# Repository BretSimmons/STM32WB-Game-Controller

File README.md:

# STM32WB Game Controller

Custom microcontroller for running embedded games and other programming projects.

**Functionality:**

My original idea for this board was to create a microcontroller to run an embedded pong game I wrote a few months ago [(here)](https://github.com/BretSimmons/Embedded-Pong). I ended up adding the requried perhipherals (I2C, ADC, and 4 GPIO pins), but also UART, and a connector for an RF antenna. I wanted to create a multi purpose microcontroller I can use in future projects, and gain experience impedence matching traces for high frequencies.

**How It Works:**

The board is powered by an USB-C header and runs through ESD protection and a step down voltage regulator to power the STM32WB55xx MCU. The MCU can be programmed via either the USB or a Tag Connect header. The MCU contains several internal clocks, and I additionally included an external crystal oscillator. The perhipherals can be configured via software, and routed out via the Molex headers on the board. 

**Future Updates:**

This project is a work in progress, and there are still a couple of changes I want to make before ordering the PCB. Once I have it ordered and assembled I will update this repo with a video demo.

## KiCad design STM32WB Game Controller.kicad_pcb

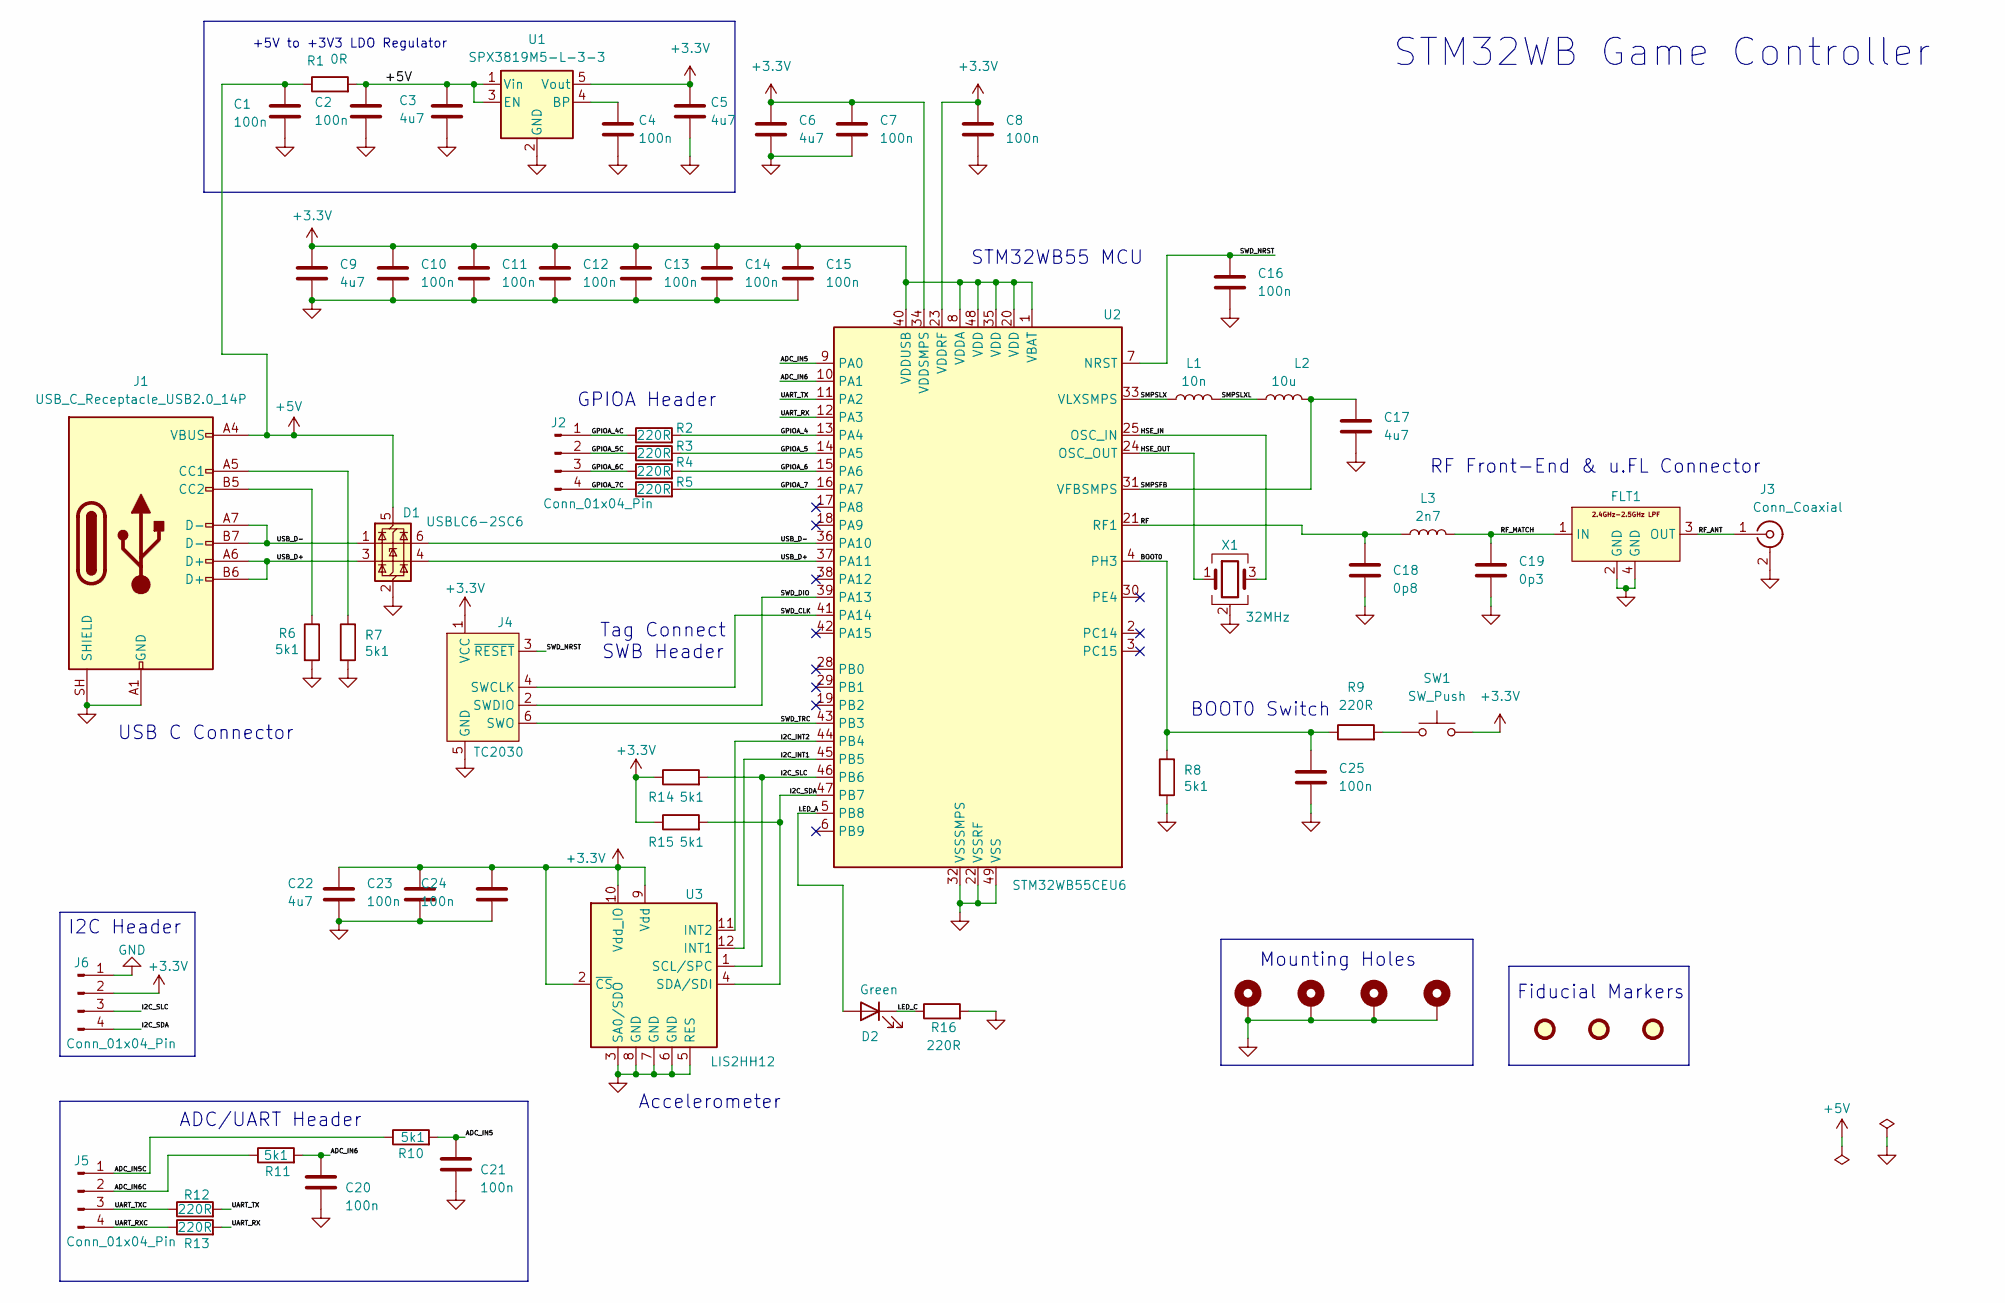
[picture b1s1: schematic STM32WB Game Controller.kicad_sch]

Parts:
C1, C2, C4, C7, C8, C10, C11, C12, C13, C14, C15, C16, C20, C21, C23, C24, C25: 100n; C_0603_1608Metric; Manufacturer Part Number CC0603JRX7R9BB104
C3, C5, C6, C9, C17, C22: 4u7; C_0805_2012Metric; Manufacturer Part Number CL21A475KPFNNNE
C18: 0p8; C_0603_1608Metric; Manufacturer Part Number CC0603BRNPO9BNR80
C19: 0p3; C_0603_1608Metric; Manufacturer Part Number 0603N0R3C500CT
D1: USBLC6-2SC6; SOT-23-6; Manufacturer Part Number USBLC6-2SC6
D2: Green; LED_0603_1608Metric; Manufacturer Part Number KT EELP41.12-S2U1-25-2X4X-5-R18
FID1, FID2, FID3: Fiducial; Fiducial_1mm_Mask2mm
FLT1: DLF162500LT-5028A1; Manufacturer Part Number DLF162500LT-5028A1
H1, H2, H3, H4: MountingHole_Pad; MountingHole_2.2mm_M2_Pad
J1: USB_C_Receptacle_USB2.0_14P; USB_C_Receptacle_GCT_USB4105-xx-A_16P_TopMnt_Horizontal; Manufacturer Part Number USB4105-GF-A
J2, J5, J6: Conn_01x04_Pin; Molex_PicoBlade_53048-0410_1x04_P1.25mm_Horizontal; Manufacturer Part Number 53048-0410
J3: Conn_Coaxial; U.FL_Hirose_U.FL-R-SMT-1_Vertical; Manufacturer Part Number U.FL-R-SMT(01)
J4: TC2030; Tag-Connect_TC2030-IDC-FP_2x03_P1.27mm_Vertical
L1: 10n; L_0603_1608Metric; Manufacturer Part Number LCCI0603J10NGTAR
L2: 10u; L_0805_2012Metric; Manufacturer Part Number MLZ2012M100WT000
L3: 2n7; L_0603_1608Metric; Manufacturer Part Number MCL1608V2-2R7-R
R1: 0R; R_0603_1608Metric; Manufacturer Part Number AF0603JR-130RL
R2, R3, R4, R5, R9, R12, R13, R16: 220R; R_0603_1608Metric; Manufacturer Part Number AF0603FR-07220RL
R6, R7, R8, R10, R11, R14, R15: 5k1; R_0603_1608Metric; Manufacturer Part Number RC0603FR-105K1L
SW1: SW_Push; SW_SPST_CK_RS282G05A3; Manufacturer Part Number RS-282G05A3-SM RT
U1: SPX3819M5-L-3-3; SOT-23-5; Manufacturer Part Number SPX3819M5-L-3-3/TR
U2: STM32WB55CEU6; QFN-48-1EP_7x7mm_P0.5mm_EP5.6x5.6mm; Manufacturer Part Number STM32WB55CEU6
U3: LIS2HH12; LGA-12_2x2mm_P0.5mm; Manufacturer Part Number LIS2HH12TR
X1: 32MHz; Crystal_SMD_2016-4Pin_2.0x1.6mm; Manufacturer Part Number CX2016SA32000F0HPQG1

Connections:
+3.3V: C5.1, C6.1, C7.1, C8.1, C9.1, C10.1, C11.1, C12.1, C13.1, C14.1, C15.1, C22.1, C23.1, C24.1, J4.1 (VCC), J6.2, R14.1, R15.1, SW1.2, U1.5 (Vout), U2.1 (VBAT), U2.8 (VDDA), U2.20 (VDD), U2.23 (VDDRF), U2.34 (VDDSMPS), U2.35 (VDD), U2.40 (VDDUSB), U2.48 (VDD), U3.2 (~CS), U3.9 (Vdd), U3.10 (Vdd_IO)
+5V: C1.1, C2.1, C3.1, D1.5 (VBUS), J1.A4 (VBUS), J1.A9 (VBUS), J1.B4 (VBUS), J1.B9 (VBUS), R1.1, R1.2, U1.1 (Vin), U1.3 (EN)
/ADC_IN5: C21.1, R10.2, U2.9 (PA0)
/ADC_IN5C: J5.1, R10.1
/ADC_IN6: C20.1, R11.2, U2.10 (PA1)
/ADC_IN6C: J5.2, R11.1
/BOOT0: C25.1, R8.1, R9.1, U2.4 (PH3)
/GPIOA_4: R2.2, U2.13 (PA4)
/GPIOA_4C: J2.1, R2.1
/GPIOA_5: R3.2, U2.14 (PA5)
/GPIOA_5C: J2.2, R3.1
/GPIOA_6: R4.2, U2.15 (PA6)
/GPIOA_6C: J2.3, R4.1
/GPIOA_7: R5.2, U2.16 (PA7)
/GPIOA_7C: J2.4, R5.1
/HSE_IN: U2.25 (OSC_IN), X1.3
/HSE_OUT: U2.24 (OSC_OUT), X1.1
/I2C_INT1: U2.45 (PB5), U3.12 (INT1)
/I2C_INT2: U2.44 (PB4), U3.11 (INT2)
/I2C_SDA: J6.4, R15.2, U2.47 (PB7), U3.4 (SDA/SDI)
/I2C_SLC: J6.3, R14.2, U2.46 (PB6), U3.1 (SCL/SPC)
/LED_A: D2.2 (A), U2.5 (PB8)
/LED_C: D2.1 (K), R16.1
/RF: C18.1, L3.1, U2.21 (RF1)
/RF_ANT: FLT1.3 (OUT), J3.1 (In)
/RF_MATCH: C19.1, FLT1.1 (IN), L3.2
/SMPSFB: C17.1, L2.2, U2.31 (VFBSMPS)
/SMPSLX: L1.1, U2.33 (VLXSMPS)
/SMPSLXL: L1.2, L2.1
/SWD_CLK: J4.4 (SWCLK), U2.41 (PA14)
/SWD_DIO: J4.2 (SWDIO), U2.39 (PA13)
/SWD_NRST: C16.1, J4.3 (~RESET), U2.7 (NRST)
/SWD_TRC: J4.6 (SWO), U2.43 (PB3)
/UART_RX: R13.2, U2.12 (PA3)
/UART_RXC: J5.4, R13.1
/UART_TX: R12.2, U2.11 (PA2)
/UART_TXC: J5.3, R12.1
/USB_D+: D1.3 (I/O2), D1.4 (I/O2), J1.A6 (D+), J1.B6 (D+), U2.37 (PA11)
/USB_D-: D1.1 (I/O1), D1.6 (I/O1), J1.A7 (D-), J1.B7 (D-), U2.36 (PA10)
GND: C1.2, C2.2, C3.2, C4.2, C5.2, C6.2, C7.2, C8.2, C9.2, C10.2, C11.2, C12.2, C13.2, C14.2, C15.2, C16.2, C17.2, C18.2, C19.2, C20.2, C21.2, C22.2, C23.2, C24.2, C25.2, D1.2 (GND), FLT1.2 (GND), FLT1.4 (GND), H1.1 (1_1), H2.1 (1_1), H3.1 (1_1), H4.1 (1_1), J1.A1 (GND), J1.A12 (GND), J1.B1 (GND), J1.B12 (GND), J1.SH (SHIELD), J3.2 (Ext), J4.5 (GND), J6.1, R6.2, R7.2, R8.2, R16.2, U1.2 (GND), U2.22 (VSSRF), U2.32 (VSSSMPS), U2.49 (VSS), U3.3 (SA0/SDO), U3.5 (RES), U3.6 (GND), U3.7 (GND), U3.8 (GND), X1.2 (G), X1.4 (G)
unnamed: J1.A5 (CC1), R7.1
unnamed: J1.B5 (CC2), R6.1
unnamed: R9.2, SW1.1
unnamed: C4.1, U1.4 (BP)

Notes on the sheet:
RF Front-End & u.FL Connector
BOOT0 Switch
Accelerometer
ADC/UART Header
Mounting Holes
Tag Connect SWB Header
GPIOA Header
STM32WB Game Controller
STM32WB55 MCU
+5V to +3V3 LDO Regulator
I2C Header
Fiducial Markers
USB C Connector

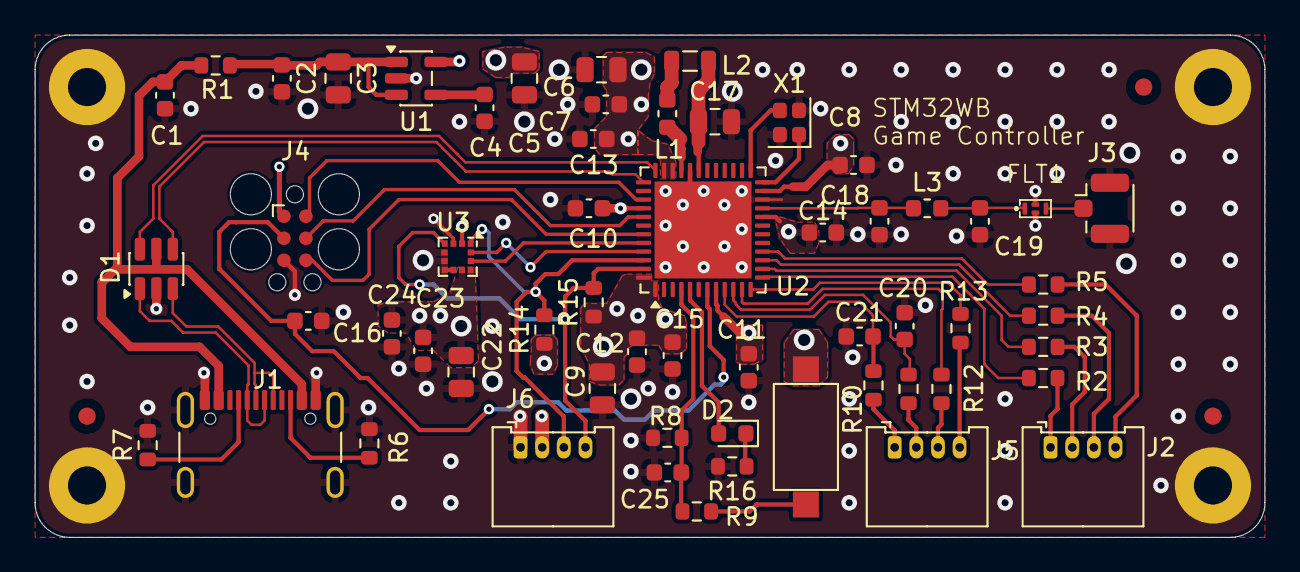
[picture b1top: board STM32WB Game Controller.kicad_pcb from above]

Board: 4 copper layers, 71.0 x 29.0 mm, 65 parts (0 on the bottom side), 44 nets.

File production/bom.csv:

Designator,Footprint,Quantity,Value,LCSC Part #
"C1, C10, C11, C12, C13, C14, C15, C16, C2, C20, C21, C23, C24, C25, C4, C7, C8",0603,17,100n,
"C17, C22, C3, C5, C6, C9",0805,6,4u7,
C18,0603,1,0p8,
C19,0603,1,0p3,
D1,SOT-23-6,1,USBLC6-2SC6,
D2,0603,1,Green,
FLT1,DLF162500LT-5028A1,1,DLF162500LT-5028A1,
J1,USB_C_Receptacle_GCT_USB4105-xx-A_16P_TopMnt_Horizontal,1,USB_C_Receptacle_USB2.0_14P,
"J2, J5, J6",Molex_PicoBlade_53048-0410_1x04_P1.25mm_Horizontal,3,Conn_01x04_Pin,
J3,U.FL_Hirose_U.FL-R-SMT-1_Vertical,1,Conn_Coaxial,
L1,0603,1,10n,
L2,0805,1,10u,
L3,0603,1,2n7,
R1,0603,1,0R,
"R10, R11, R14, R15, R6, R7, R8",0603,7,5k1,
"R12, R13, R16, R2, R3, R4, R5, R9",0603,8,220R,
SW1,SW_SPST_CK_RS282G05A3,1,SW_Push,
U1,SOT-23-5,1,SPX3819M5-L-3-3,
U2,QFN-48-1EP_7x7mm_P0.5mm_EP5.6x5.6mm,1,STM32WB55CEU6,
U3,LGA-12_2x2mm_P0.5mm,1,LIS2HH12,
X1,Crystal_SMD_2016-4Pin_2.0x1.6mm,1,32MHz,
